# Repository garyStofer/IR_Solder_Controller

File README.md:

# IR_Solder_Controller
IR reflow solder temperature controller

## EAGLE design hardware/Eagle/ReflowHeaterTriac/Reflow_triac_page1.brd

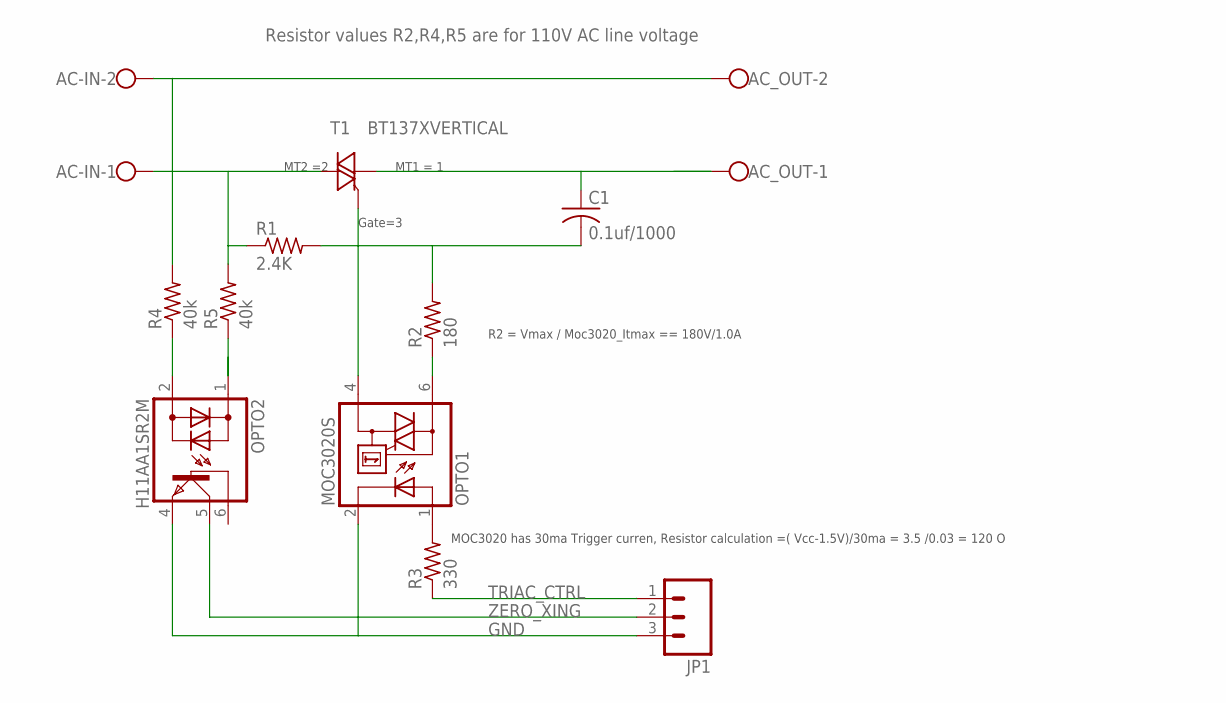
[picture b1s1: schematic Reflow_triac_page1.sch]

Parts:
AC-IN: W237-102
AC_OUT: W237-102
C1: 0.1uf/1000; C102_152-062X184
JP1: M03PTH; 1X03
OPTO1: MOC3020S; DIL6-SMD
OPTO2: H11AA1SR2M; DIL6-SMD
R1: 2.4K; 0207/10
R2: 180; 0207/10
R3: 330; 0207/10
R4, R5: 40k; 0207/10
T1: BT137XVERTICAL; TO220DS

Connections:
GND: JP1.3, OPTO1.2 (C), OPTO2.4 (E)
unnamed: AC-IN.1, R1.1, R5.2, T1.A2
unnamed: AC_OUT.1, C1.1, T1.A1
unnamed: OPTO1.4 (A1), T1.G
unnamed: C1.2, R1.2, R2.2
unnamed: OPTO1.6 (A2), R2.1
unnamed: OPTO1.1 (A), R3.2
unnamed: OPTO2.2 (AC2), R4.1
unnamed: AC-IN.2, AC_OUT.2, R4.2
unnamed: OPTO2.1 (AC1), R5.1
TRIAC_CTRL: JP1.1, R3.1
ZERO_XING: JP1.2, OPTO2.5 (C)

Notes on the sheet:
R2 = Vmax / Moc3020_Itmax == 180V/1.0A
MOC3020 has 30ma Trigger curren, Resistor calculation =( Vcc-1.5V)/30ma = 3.5 /0.03 = 120 O
MT1 = 1
MT2 =2
Gate=3
Resistor values R2,R4,R5 are for 110V AC line voltage

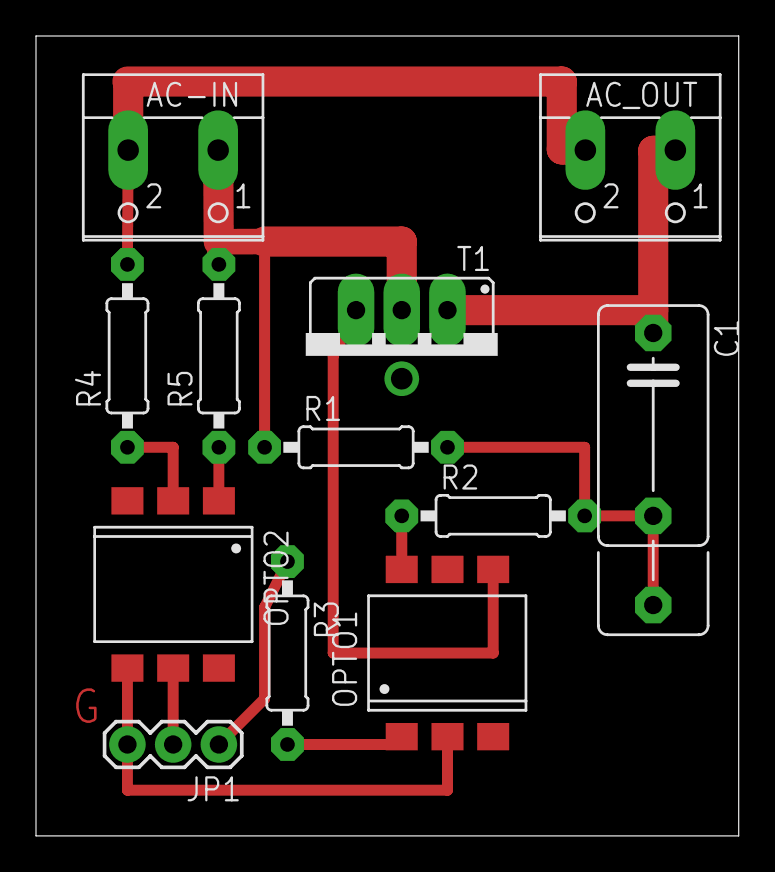
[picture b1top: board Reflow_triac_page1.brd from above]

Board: 2 copper layers, 39.0 x 44.4 mm, 12 parts (0 on the bottom side), 12 nets.

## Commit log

2017-09-22 Changed start-up screen and version label. Added readme.txt for lamp housing. Clarified where PCB cad files are.

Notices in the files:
parts and their libraries:
SparkFun-Connectors: Licensing: CC v3.0 Share-Alike You are welcome to use this library for commercial purposes.
